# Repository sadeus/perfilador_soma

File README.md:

# Perfilador/Polarimetro SOMA

## Contenido
Se crearon sensores optomecánicos portátiles, para poder medir cambios de los haces de los setups del laboratorio. Todo el marco del proyecto SOMA

### Indice de carpetas
- software: Software para la adquisición y visualización de las mediciones. Acá se efectúa el análisis de los datos obtenidos
- firmware: Código para el uC para el polarimetro/perfilador. Tiene un makefila con los métodos usuales
- circuito: Diseño del circuito impreso
- perfilador: Diseño mecánico del perfilador
- polarimetro: Diseño mecánico del polarimetro
- espectrometro: Diseño del circuito para el espectrómetro (EN PROGRESO)

## Instalación

Para poder instalar y usar el software/firmware de este proyecto es necesario tener [NodeJS](https://nodejs.org/es/):

- Linux, macOS: Instalación por manejador de paquetes, [aquí](https://nodejs.org/es/download/package-manager/)
- Windows: Descargar binario de la página oficial

En una command prompt o terminal escribir lo siguiente para instalar dependencias

```npm install```

Esto instala las dependencias de firmware y software. Para obtener ayuda de los comandos disponibles ejecutar

```npm run```

### Lista de comandos
- `npm run ip`: abre el puerto serie creado al conectar el uC y obtiene la ip del dispositivo
- `npm run start`: inicia el servidor web del software de adquisición. Por defecto se entra en un browser en http://localhost:9000
- `npm run compile`: compila el firmware. Para compilar el firmware, por ahora, es necesario logearse con `npm run login` y una cuenta de [particle.io](http://build.particle.io)
- `npm run upload`: Actualiza el firmware del uC por USB. Es necesario tener el uC en modo DFU (ver [acá](https://docs.particle.io/guide/getting-started/modes/photon/#dfu-mode-device-firmware-upgrade-))

## Dependencias

### Software
- Python v3.5.0
- Numpy v1.11.3
- Pandas v0.19.2
- Matplotlib v2.0.0
- Scipy v0.18.1
- Flask v0.12
- Web browser (Firefox, Chrome, Safari, _no funciona en IE_)

### Firmware
Para compilar, flashear y escuchar el puerto Serie del uC es necesario tener:
- NodeJS v6.0
- Particle-cli v1.21.0
- readline-sync (para interfaz interactiva)

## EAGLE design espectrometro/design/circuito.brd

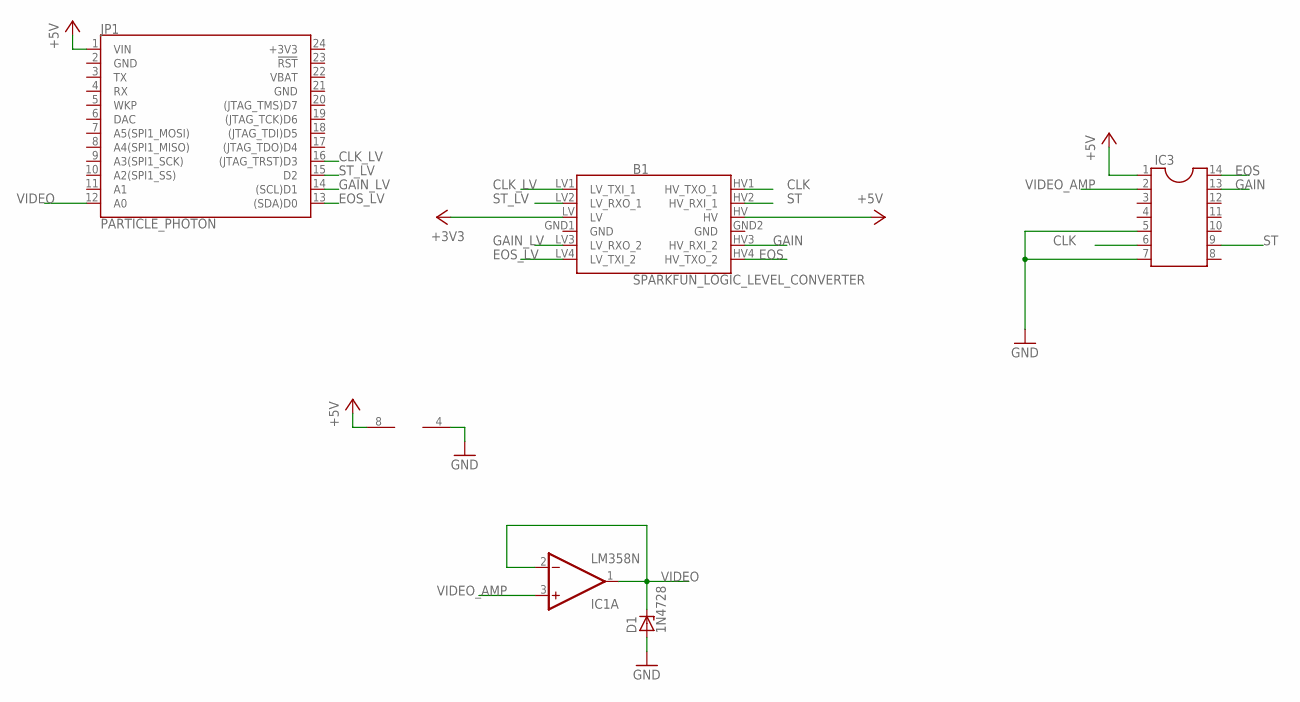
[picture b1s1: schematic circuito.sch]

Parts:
B1: SPARKFUN_LOGIC_LEVEL_CONVERTER
D1: 1N4728; DO41Z10
IC1: LM358N; DIL08
IC3: DIL14S; SOCKET-14
JP1: PARTICLE_PHOTON

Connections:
+3V3: B1.LV, JP1.24 (+3V3)
+5V: B1.HV, IC1.8 (V+), IC3.1, JP1.1 (VIN)
CLK: B1.HV1 (HV_TXO_1), IC3.6
CLK_LV: B1.LV1 (LV_TXI_1), JP1.16 ((JTAG_TRST)D3)
EOS: B1.HV4 (HV_TXO_2), IC3.14
EOS_LV: B1.LV4 (LV_TXI_2), JP1.13 ((SDA)D0)
GAIN: B1.HV3 (HV_RXI_2), IC3.13
GAIN_LV: B1.LV3 (LV_RXO_2), JP1.14 ((SCL)D1)
GND: B1.GND1 (GND), B1.GND2 (GND), D1.A, IC1.4 (V-), IC3.5, IC3.7, JP1.2 (GND), JP1.21 (GND)
ST: B1.HV2 (HV_RXI_1), IC3.9
ST_LV: B1.LV2 (LV_RXO_1), JP1.15 (D2)
VBAT: JP1.22 (VBAT)
VIDEO: D1.C, IC1.1 (OUT), IC1.2 (-IN), JP1.12 (A0)
VIDEO_AMP: IC1.3 (+IN), IC3.2

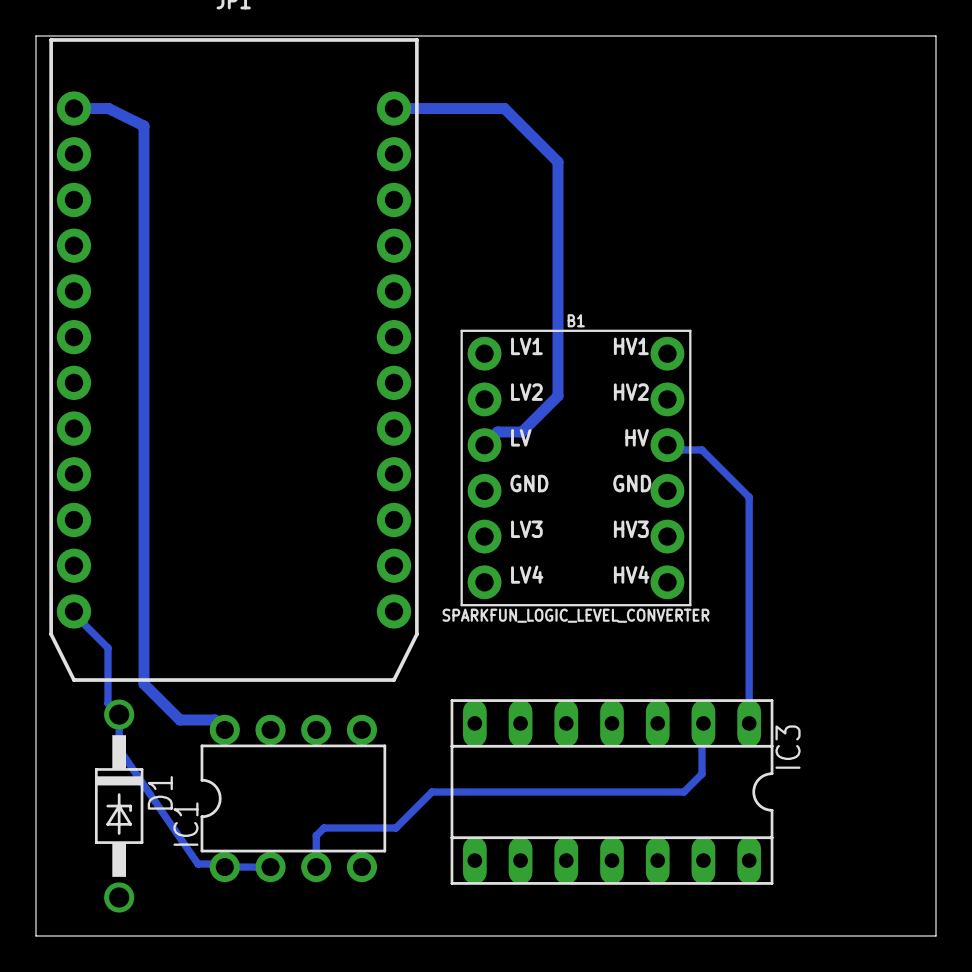
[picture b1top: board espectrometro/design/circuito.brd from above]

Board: 2 copper layers, 50.0 x 50.0 mm, 5 parts (0 on the bottom side), 13 nets.

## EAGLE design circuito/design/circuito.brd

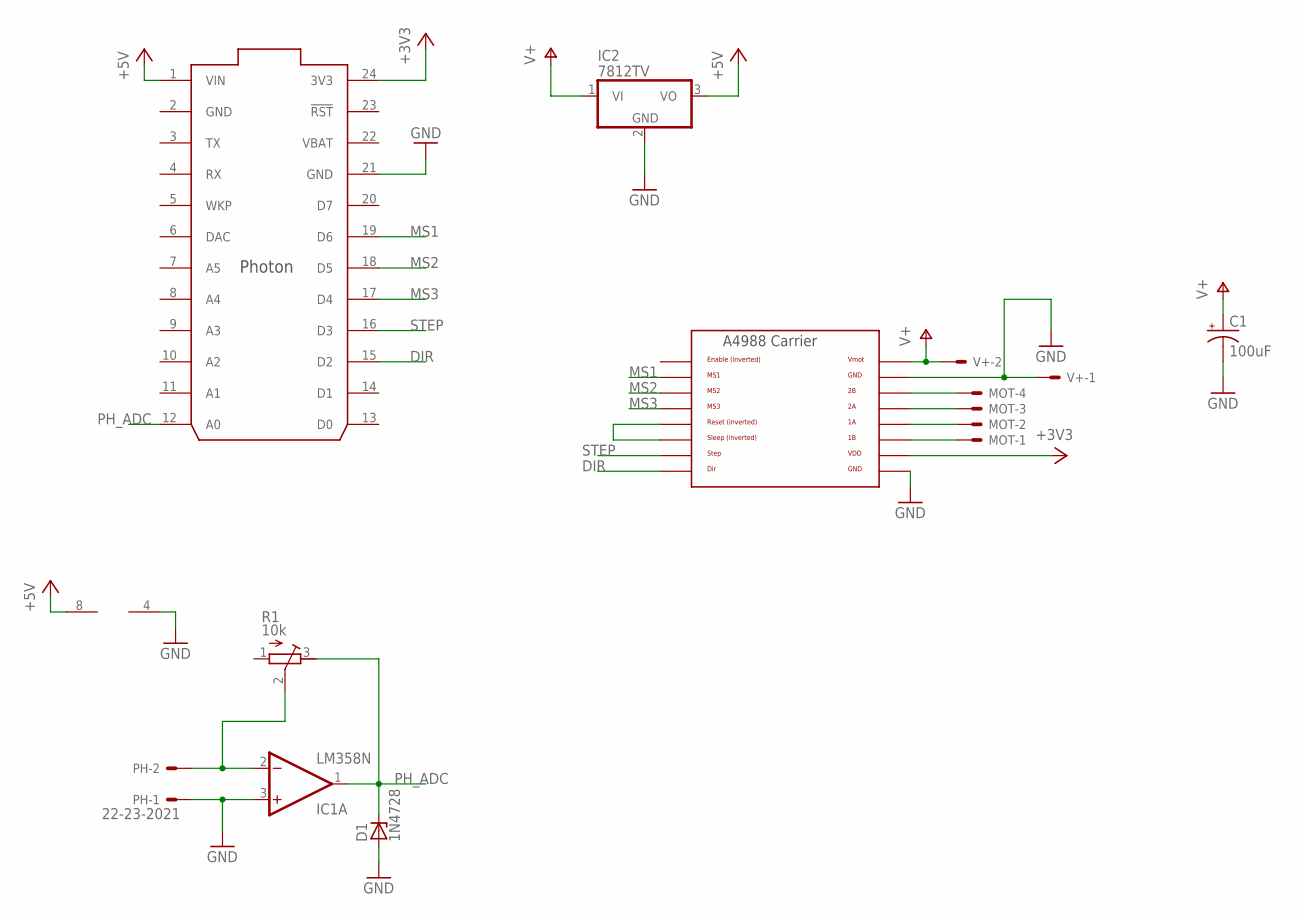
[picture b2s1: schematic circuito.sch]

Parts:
C1: 100uF; E3,5-8
D1: 1N4728; DO41Z10
IC1: LM358N; DIL08
IC2: 7812TV; TO220V
MOT: 22-23-2041
PH: 22-23-2021
R1: 10k; RTRIM64W
U$1: PHOTON_WITH_HEADERS; PHOTON
U$2: A4988BREAKOUT
V+: 22-23-2021

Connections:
+3V3: U$1.24 (3V3), U$2.VDD
+5V: IC1.8 (V+), IC2.3 (VO), U$1.1 (VIN)
DIR: U$1.15 (D2), U$2.DIR
GND: C1.-, D1.A, IC1.3 (+IN), IC1.4 (V-), IC2.2 (GND), PH.1, U$1.2 (GND), U$1.21 (GND), U$2.GND, U$2.GND@0 (GND), V+.1
MS1: U$1.19 (D6), U$2.MS1
MS2: U$1.18 (D5), U$2.MS2
MS3: U$1.17 (D4), U$2.MS3
unnamed: MOT.4, U$2.2B
unnamed: U$2.RST, U$2.SLP (SLEEP)
unnamed: MOT.1, U$2.1B
unnamed: MOT.2, U$2.1A
unnamed: MOT.3, U$2.2A
unnamed: IC1.2 (-IN), PH.2, R1.2 (S)
PH_ADC: D1.C, IC1.1 (OUT), R1.3 (E), U$1.12 (A0)
STEP: U$1.16 (D3), U$2.STEP
V+: C1.+, IC2.1 (VI), U$2.VMOT, V+.2
VBAT: U$1.22 (VBAT)

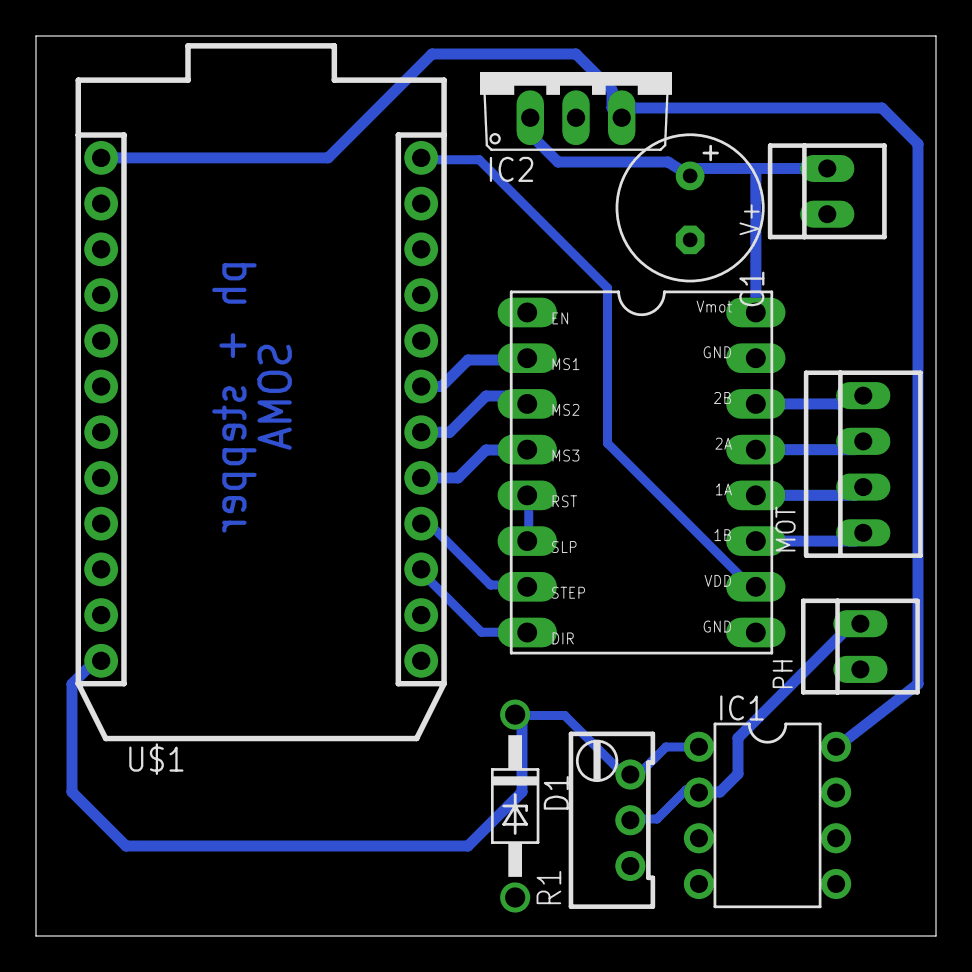
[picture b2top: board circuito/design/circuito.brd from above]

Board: 2 copper layers, 50.0 x 50.0 mm, 10 parts (0 on the bottom side), 16 nets.

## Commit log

2016-06-13 Se copia desarrollo del GDrive
2016-06-13 Se agrega mediciones, más o menos ordenadas. Se cambia README
2016-06-15 Medición con tambor de plástico
2016-06-15 Nueva iteración, agujero más grande
2016-06-15 Cambios de script menores, nueva medición
2016-06-16 Cambios de gitignore para windows
2016-06-16 Se elimina archivos de thumbnails de windows
2016-06-16 Nueva iteración de soporte
2016-06-16 Carcasa final. Va con un acrilico arriba
2016-06-18 Imagenes para presentación. Nuevos cambios en modelo
2016-06-23 Se ordenaron archivos, se creó nuevo archivo de diseño para polarimetro
2016-06-24 Cambios del engranaje. Agregado mejor interfaz web. Cambio en código de sketch, ahora es compatible con polarimetro
2016-06-30 Nuevo cambio en carcaza
2016-06-30 Se cambio velocidad para polarimetro
2016-06-30 Cambios de diseño.
2016-06-30 Mediciones sin ruido finales. Polarización definida
2016-06-30 Implementación con PyQT en progreso
2016-07-01 Se agrega etiquetas del preprocesador para usar polarimetro y perfilador en la compilación
2016-07-01 Ajustes hechos para datos nuevos
2016-07-01 Commit de charla
2016-07-01 Datos viejos agregados
2016-07-01 Nuevo gitignore
2016-07-01 Medición de spim con plástico PLA
2016-07-01 Mediciones de diferentes laseres, azul y verde
2016-07-01 Cambio de titulo de la charla
2016-07-04 Primer iteración de charla final labo 7
2016-07-05 Segunda iteración y presentación de charla final labo 7
2016-07-12 Nuevos diseños, más archivos dwg/dxf con planos mecánicos
2016-07-12 Cambios en mediciones de perfil
2016-07-15 Cambio final del circuito.
2016-07-15 Reordenado de archivos de informes. Anteúltima iteración del informe final.
2016-07-16 Nueva iteración del informe. Preprint
2016-07-19 Iteración final del informe
2016-09-12 Cambio menor de gui
2016-09-12 Se eliminan archivos binarios
2016-09-12 Cambios menores
2016-09-13 Primer commit de documentación
2016-09-13 Se comprime charla final de laboratorio 7
2016-09-13 Archivos de charla final
2016-09-13 Se comprime archivos de informe de laboratorio 7
2016-09-13 Se agrega documentación
2016-10-05 Primera iteraciÃn del manual
2016-10-11 Circuito funcionando, imprime IP por puerto serie
2016-10-11 Última iteración
2016-10-11 Nueva iteración del manual
2016-10-23 Interfaz funcional, solo crudo
2016-10-23 Sensores funcionando con ip dinámica
2016-11-08 Implementación con 7805
2016-11-08 Web funcionando con uC
2016-12-28 Mejora en interfaz, redescubrimiento de sensor en segmento de red
2016-12-28 Esquemático en formato EAGLE
2017-01-01 Uso de web workers para interfaz web
2017-01-01 Uso de IP en Cloud, a nivel uC
2017-01-01 Cambio de código
2017-01-01 Se organizan views
2017-04-07 Ordenado de archivos
2017-04-07 PDF de ph+motor
2017-04-07 Cambios en makefile, usa node local. Cambios de código
2017-04-07 Cambios en visor web
2017-04-07 Diseño de espectrometro
2017-04-10 Ordenado de adquisición
2017-04-11 Ordenado de web y mejora de esta. Se puede setear la IP
2017-04-11 Reordenado de firmware. Compila y funciona
2017-04-11 Mejora del README con el reordenado. Mas docs
2017-04-11 Firmware corriendo
2017-04-11 Requirements
2017-04-16 Building por npm
2017-04-16 Se pasa a usar assets locales

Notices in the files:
parts and their libraries:
SparkFun-Boards: Licensing: Creative Commons ShareAlike 4.0 International - https://creativecommons.org/licenses/by-sa/4.0
